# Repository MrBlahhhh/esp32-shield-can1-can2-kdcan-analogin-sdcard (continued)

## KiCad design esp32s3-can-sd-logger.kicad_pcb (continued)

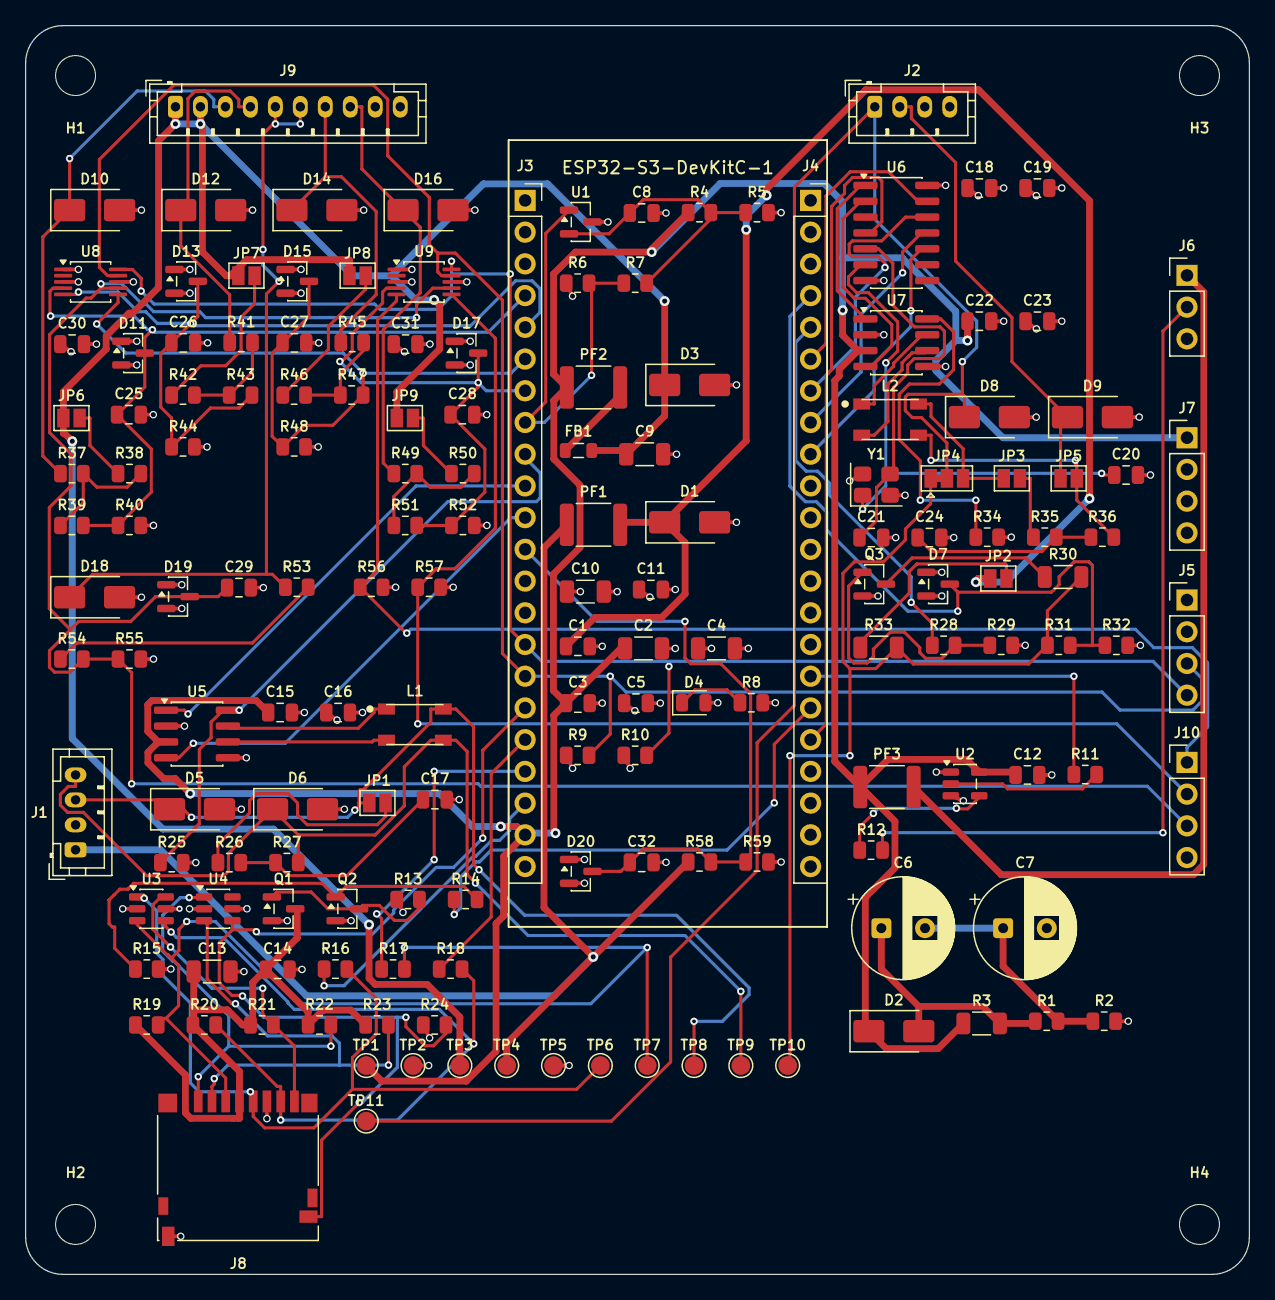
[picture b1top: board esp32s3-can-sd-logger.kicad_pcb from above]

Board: 4 copper layers, 98.0 x 100.0 mm, 164 parts (0 on the bottom side), 88 nets.

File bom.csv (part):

Qty (1 board),Qty (10 boards),References,Value,Voltage,Tolerance,Footprint,Manufacturer part number,LCSC,Notes
1,10,C1,100nF,100V,,Capacitor_SMD:C_0805_2012Metric,,C28233,
2,20,C17 C24,4.7nF,50V,,Capacitor_SMD:C_0805_2012Metric,,C1744,Split-termination common-mode stabiliser
1,10,C19,1uF,16V,,Capacitor_SMD:C_0805_2012Metric,,C28323,MCP2518FD bulk
2,20,C2 C4,22uF,16V,,Capacitor_SMD:C_1206_3216Metric,,C12891,Bulk at the 5 V socket pin
2,20,C20 C21,15pF,50V,,Capacitor_SMD:C_0805_2012Metric,,C1794,"Crystal load cap, sized for Y1's 12 pF CL: C1=C2=2*(CL - Cstray) = 2*(12 - 5) = 14 pF, and 15 pF is the nearest E-series value. Re-check this if the crystal is substituted -- CL varies part to part, and an oscillator that starts on the bench but not at -20 C is the classic way to get it wrong"
5,50,C25 C26 C27 C28 C29,470nF,50V,,Capacitor_SMD:C_0805_2012Metric,,C13967,"Ch1 anti-alias. 470nF, not the 100nF this inherited: source impedance here is (1k+10k)||2.21k = 1.84k, so 100nF puts the corner at 865 Hz -- above the 430 Hz Nyquist of the ADS1115 at 860 SPS, and well above anything the ESP32's own SAR ADC can sample cleanly. That was survivable while 0-5 V was the default range (261 Hz) and became the only behaviour when the range jumpers went. 470nF gives 184 Hz, which still passes anything a wideband does and stops engine noise folding into the log"
13,130,C11 C12 C14 C15 C16 C18 C22 C23 C3 C30 C31 C32 C5,100nF,16V,,Capacitor_SMD:C_0805_2012Metric,,C49678,
2,20,C6 C7,0.33F,2.7V,,Capacitor_THT:CP_Radial_D8.0mm_P3.50mm,Eaton HB1030-2R5105-R,,"Hold-up cell 1 of 2 in series -> 0.165 F at 5.4 V, which is 825 ms with the strip shed. 1 F was the first pick and bought 2500 ms that nothing needs: the parent board shipped 127 ms and that was judged adequate, a healthy card flushes in 18 ms, and the worst stall gen/simulate_firmware.py models is 500 ms. This is still six times the parent's margin and it is the most expensive line on the board -- see docs/COST.md. ESR must be under about 1 ohm; cylindrical cells are around 200 mohm, coin-type EDLCs are 30-200 OHM and will not work here"
1,10,C8,1nF,50V,,Capacitor_SMD:C_0805_2012Metric,,C46653,Keeps switching noise off the reference
3,30,C10 C13 C9,10uF,16V,,Capacitor_SMD:C_1206_3216Metric,,C13585,
5,50,D1 D5 D6 D8 D9,SMAJ26CA,,,Diode_SMD:D_SMA,Diodes Inc SMAJ26CA-13-F,C134976,"Clamps the OBD 12 V node. 400 W is enough here, not the parent's 1500 W SMC: nothing downstream draws more than 25 mA, so there is no load-dump energy to carry into a converter -- only a clamp to hold"
5,50,D10 D12 D14 D16 D18,SMAJ40CA,,,Diode_SMD:D_SMA,Littelfuse SMAJ40CA,C223989,"Ch1 harness transient clamp (bidirectional, 400W)"
1,10,D2,SS14,,,Diode_SMD:D_SMA,SS14,C2480,"Discharge path, bypassing the charge resistor. Anode on the bank, cathode on the rail: it conducts only once the rail has sagged a diode drop below the bank, which is exactly when the supply has gone away"
1,10,D3,SMAJ6.0A,,,Diode_SMD:D_SMA,Littelfuse SMAJ6.0A,C223993,"Clamps harness-injected transients on the sensor 5V. 6.0V standoff, not 5.0V: a 5.0V part on a 5.0V rail leaks up to 800uA continuously"
1,10,D4,green,,,LED_SMD:LED_0805_2012Metric,,C2297,"Shield 3V3 is up, which means the dev board is in its socket the right way round and its LDO is running"
7,70,D11 D13 D15 D17 D19 D20 D7,BAT54S,,,Package_TO_SOT_SMD:SOT-23,MDD BAT54S,C408389,"RX clamp. This one is not optional -- it conducts on every recessive bit above 11.5 V of battery, which is most of them"
1,10,FB1,600R,,,Inductor_SMD:L_0805_2012Metric,Wurth 742792022,C2661452,
4,40,H1 H2 H3 H4,M3,,,MountingHole:MountingHole_3.2mm_M3,,,
1,10,J1,CAN1 + power harness,,,Connector_JST:JST_PH_B4B-PH-K_1x04_P2.00mm_Vertical,JST B4B-PH-K-S(LF)(SN),C131334,"OBD-II pins 16/4/6/14. Pin 1 is sense only -- the board is powered from the dev board's USB-C, not from here"
1,10,J10,Spare diff in,,,Connector_PinHeader_2.54mm:PinHeader_1x04_P2.54mm_Vertical,,,"The second ADC's unused pair, brought out raw -- 0-3.3V only, no divider and no clamp in front of them. For a bench sensor, not for the loom"
1,10,J2,Aux bus harness,,,Connector_JST:JST_PH_B4B-PH-K_1x04_P2.00mm_Vertical,JST B4B-PH-K-S(LF)(SN),C131334,"The second port. What these two pins carry is a solder-jumper choice: K-line on AUX_A (the default, which is what an R53 wants), or the second CAN pair. See AUXSEL and AUXCL on the CAN sheet"
1,10,J3,DevKit J1,,,Connector_PinSocket_2.54mm:PinSocket_1x22_P2.54mm_Vertical,ESP32-S3-DevKitC-1 J1,,"Mirrors DevKitC-1 J1. Pins 1-2 (3V3) and 21 (5V) are both INPUTS to the shield. Analog on 4-7 and 12, CAN on 9-11, SD bus on 15-20 -- grouped so each block routes away from the row rather than across it. Pin 3 is RST, pins 13/14 are IO3/IO46, all left open."
1,10,J4,DevKit J3,,,Connector_PinSocket_2.54mm:PinSocket_1x22_P2.54mm_Vertical,ESP32-S3-DevKitC-1 J3,,"Mirrors DevKitC-1 J3. K-line on 4/5, the second CAN's SPI on 6-9 with its interrupt on 18, WS2812 on 16. Pin 17 is SD_PWR_EN, the one net that crosses to the other side of the board, and it goes round the end of the row. Pin 10 (IO38) is left open because it drives the dev board's RGB LED on v1.1; check the revision, some put it on IO48, which is the WS2812 output here."
1,10,J5,I2C / Qwiic,,,Connector_PinHeader_2.54mm:PinHeader_1x04_P2.54mm_Vertical,,,External I2C sensors. Kept because the dev board has no Qwiic connector of its own
1,10,J6,WS2812,,,Connector_PinHeader_2.54mm:PinHeader_1x03_P2.54mm_Vertical,,,Shift-light header: +5V / 5V-logic DIN / GND
1,10,J7,Rail break-out,,,Connector_PinHeader_2.54mm:PinHeader_1x04_P2.54mm_Vertical,,,
1,10,J8,microSD push-pull,,,Connector_Card:microSD_HC_Hirose_DM3D-SF,Hirose DM3D-SF,C719027,Push-pull socket; DET is the card-present switch
1,10,J9,Sensor harness,,,Connector_JST:JST_PH_B10B-PH-K_1x10_P2.00mm_Vertical,JST B10B-PH-K-S(LF)(SN),C158038,"Two 5V excitation pins, two Kelvin sense-ground pins, two current-carrying grounds, four signals. SENS_RTN must land on the SENSOR's ground stud, not on the same stud as pins 9/10"
1,10,JP1,TERM,,,Jumper:SolderJumper-2_P1.3mm_Open_Pad1.0x1.5mm,,,"Ships OPEN: unterminated. Bridge the pads only when this board is an END node on its own bus. A vehicle's bus -- OBD-II diagnostics included -- is already terminated at both ends, and a third 120 ohm across the pair takes it to about 40 ohm and can stop it working. Defaulting terminated made that an easy mistake to make"
1,10,JP2,KPU,,,Jumper:SolderJumper-2_P1.3mm_Open_Pad1.0x1.5mm,,,Ships OPEN. Bridge only if a module will not answer without a tester pull-up on the K-line
1,10,JP3,TERM2,,,Jumper:SolderJumper-2_P1.3mm_Open_Pad1.0x1.5mm,,,"Ships OPEN, for the same reason TERM does: a vehicle bus is already terminated at both ends"
1,10,JP4,AUXSEL,,,Jumper:SolderJumper-3_P1.3mm_Bridged12_Pad1.0x1.5mm,,,"Ships BRIDGED 1-2 = K-line on harness pin 5, which is what an R53 wants. For the second CAN instead: cut 1-2, bridge 2-3, and close AUXCL below. Both, or neither, is a bus that does not work"
1,10,JP5,AUXCL,,,Jumper:SolderJumper-2_P1.3mm_Open_Pad1.0x1.5mm,,,"The second half of AUXSEL. Open in K-line mode, which also leaves the second transceiver looking at an open circuit -- harmless, but firmware must not enable CAN2 there or it will bus-off waiting for an ACK that cannot come"
1,10,JP6,PULLUP1,,,Jumper:SolderJumper-2_P1.3mm_Open_Pad1.0x1.5mm,,,"Close for 2-wire NTC / open-collector sensors. Nothing to do with the input range -- it is about what kind of sensor is on the other end, not how many volts it swings"
1,10,JP7,PULLUP2,,,Jumper:SolderJumper-2_P1.3mm_Open_Pad1.0x1.5mm,,,"Close for 2-wire NTC / open-collector sensors. Nothing to do with the input range -- it is about what kind of sensor is on the other end, not how many volts it swings"
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
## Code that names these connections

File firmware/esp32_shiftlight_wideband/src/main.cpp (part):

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#define LED_TYPE    WS2812B
#define COLOR_ORDER GRB

#define CAN_TX_PIN  GPIO_NUM_17
#define CAN_RX_PIN  GPIO_NUM_18
#define CAN_S_PIN   16            // low = normal, high = listen-only

#define PWR_FAIL_PIN 15           // rising = the 5 V rail is below 4.20 V

// K-line, not yet driven. Listed so the pin map in this file stays the whole
// pin map -- a GPIO that is documented nowhere is a GPIO someone reuses.
#define K_TX_PIN      2           // low-side FET gate; UART TX must be inverted
#define K_RX_PIN      1           // divided 22k/10k and clamped

// Second CAN bus: an MCP2518FD on SPI, because the ESP32-S3 has exactly one
// TWAI peripheral and two buses have to be watched at once. Not driven by
// this sketch yet; listed so the pin map in this file stays the whole pin
// map. SDI/SDO on the controller are named from ITS point of view, so they
// cross over: the controller's SDI is this end's MOSI.
#define CAN2_SCK_PIN  39
#define CAN2_MOSI_PIN 40          // -> MCP2518FD SDI
#define CAN2_MISO_PIN 41          // <- MCP2518FD SDO
#define CAN2_CS_PIN   42
#define CAN2_INT_PIN  21
// These two live on the far socket row from the card itself. They are the
// only SD signals that do, and deliberately: they are DC, so crossing the
// board costs nothing, while the six bus lines stay beside the slot.
#define SD_PWR_EN_PIN 47
#define SD_CD_PIN     11
// 1-BIT SDMMC. D1/D2/D3 are not wired to the MCU at all: those three pins
// went to the second CAN controller's SPI bus, which needed five and had
// two spare. The card still pulls all three up -- a card samples DAT3 at
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// there. 1-bit carries about 1.5 MB/s against this logger's <130 kB/s, and
// bus width does not touch the card's internal write stall, which is the
// thing the whole hold-up budget is sized around.
#define SD_CLK_PIN 14
#define SD_CMD_PIN 13
#define SD_D0_PIN  12

#define RPM_STALE_MS 2000         // blank the strip if CAN goes quiet

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// worst case and the ADS1115's own 0.30% is the larger term. A per-channel
// calibration would still be better, but nothing here assumes you took one.
static const float DIVIDER_GAIN = 5.9774f;
static const int   ESP_ADC_PIN  = 4;       // AIN1 = GPIO4 = ADC1_CH3
static const int   VBAT_ADC_PIN = 8;       // VBAT_SNS = GPIO8, from OBD-II pin 16
// 108.2k / 8.2k, not the 11.0 this file inherited. The schematic moved to
// 13.2:1 so a 36 V input would not saturate the ADC and the constant never
// followed, so every battery reading was 20 % low. The fwsim board model
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  // CAN_S low = normal mode. R40 already pulls it there so the transceiver is
  // sane while the MCU is in reset; drive it anyway so the state is the
  // firmware's decision and not a resistor's.
  pinMode(CAN_S_PIN, OUTPUT);
  digitalWrite(CAN_S_PIN, LOW);

  twai_general_config_t g =
      TWAI_GENERAL_CONFIG_DEFAULT(CAN_TX_PIN, CAN_RX_PIN, TWAI_MODE_NORMAL);
  g.rx_queue_len = 32;   // FastLED.show() blocks ~0.5 ms; don't drop frames in it
  twai_timing_config_t t = TWAI_TIMING_CONFIG_500KBITS();
  twai_filter_config_t f = TWAI_FILTER_CONFIG_ACCEPT_ALL();
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
// --- microSD -----------------------------------------------------------------
void sdInit() {
  pinMode(SD_CD_PIN, INPUT);
  pinMode(SD_PWR_EN_PIN, OUTPUT);
  digitalWrite(SD_PWR_EN_PIN, HIGH);       // the card supply is switched
  delay(10);                               // let the rail come up before clocking

  SD_MMC.setPins(SD_CLK_PIN, SD_CMD_PIN, SD_D0_PIN);
  if (!SD_MMC.begin("/sdcard", true)) {    // 1-bit; see the pin block above
    Serial.println("SD: mount failed");
    return;
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
/**
 * The firmware half of README section 2. The hardware guarantees roughly
 * 108 ms between PWR_FAIL and the converters dropping out; this is what spends
 * it. Order matters: the sensor rail is already off (the ISR did it), the strip
 * goes dark so it is not drawing from the bank, then the file is closed, and
 * only then is the card supply removed — with SD_MMC.end() first, because
 * dropping SD_PWR_EN while the bus pins are still driven back-feeds the card
 * through its ESD structures (README section 5).
 */
void shutdown() {
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    SD_MMC.end();
    sdUp = false;
  }
  digitalWrite(SD_PWR_EN_PIN, LOW);

  Serial.printf("PWR_FAIL at %lu ms: %lu lines flushed and closed\n", millis(), logLines);
}
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  // Armed before anything slow runs. An ignition cut during BLE bring-up is
  // still an ignition cut, and the card is not open yet but the interrupt
  // still has to be the thing that shuts the rail down.
  pinMode(PWR_FAIL_PIN, INPUT);
  attachInterrupt(digitalPinToInterrupt(PWR_FAIL_PIN), onPowerFail, RISING);

  // BLE goes first, on purpose. The BT controller wants a sizeable block of
  // internal RAM (it cannot use PSRAM) and it is the one subsystem here that
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
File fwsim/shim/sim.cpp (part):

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    fault(SEV_ERROR, "PIN_PSRAM", "GPIO%d driven, but it is octal PSRAM on this module", gpio);
  if (p && p->role == ROLE_SD_PWR_EN && level == 0 && s.sd_begun)
    fault(SEV_WARN, "SD_BACKFEED",
          "SD_PWR_EN (GPIO%d) dropped while the card is still mounted. Call SD_MMC.end() first, "
          "or the MCU keeps driving the bus into an unpowered card through its ESD structures "
          "(README section 5)",
          gpio);
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  s.can_pins_ok = true;
  if (want_tx >= 0 && tx != want_tx) {
    const PinDef* p = find_pin(tx);
    fault(SEV_ERROR, "CAN_TX_PIN",
          "TWAI TX assigned to GPIO%d (%s), but this board wires the transceiver TXD to GPIO%d -- "
          "no frames will ever arrive, and GPIO%d is now driven by the CAN controller",
          tx, p ? role_name(p->role) : "not connected", want_tx, tx);
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  }
  if (want_rx >= 0 && rx != want_rx) {
    const PinDef* p = find_pin(rx);
    fault(SEV_ERROR, "CAN_RX_PIN",
          "TWAI RX assigned to GPIO%d (%s), but this board wires the transceiver RXD to GPIO%d",
          rx, p ? role_name(p->role) : "not connected", want_rx, rx);
    s.can_pins_ok = false;
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  int cs = gpio_with_role(ROLE_CAN_S);
  if (cs >= 0 && !pin_driven(cs))
    fault(SEV_NOTE, "CAN_S_DEFAULT",
          "CAN_S (GPIO%d) left undriven; R54 pulls it low so the transceiver comes up in normal "
          "mode. Drive it high for listen-only if this node must never ACK",
          cs);
}
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  s.i2c_pins_ok = true;
  if (want_sda >= 0 && sda != want_sda) {
    const PinDef* p = find_pin(sda);
    fault(SEV_ERROR, "I2C_SDA_PIN",
          "I2C SDA brought up on GPIO%d, but on this board GPIO%d is %s (%s) and the bus is on "
          "GPIO%d. Driving it toggles that function",
          sda, sda, p ? p->net : "nothing", p ? role_name(p->role) : "not connected", want_sda);
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  }
  if (want_scl >= 0 && scl != want_scl) {
    const PinDef* p = find_pin(scl);
    fault(SEV_ERROR, "I2C_SCL_PIN",
          "I2C SCL brought up on GPIO%d, but on this board GPIO%d is %s (%s) and the bus is on "
          "GPIO%d",
          scl, scl, p ? p->net : "nothing", p ? role_name(p->role) : "not connected", want_scl);
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  int pwr = gpio_with_role(ROLE_SD_PWR_EN);
  if (pwr >= 0 && !(s.level.count(pwr) && s.level[pwr] == 1)) {
    fault(SEV_ERROR, "SD_UNPOWERED",
          "SD_MMC.begin() with SD_PWR_EN (GPIO%d) low -- the card supply is switched through "
          "Q2/Q3 and off at reset, so there is no card on the bus to answer",
          pwr);
    return false;
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  s.stop_reason = why ? why : "";
  if (s.pwr_fail_at_ms >= 0.0 && !s.pwr_fail_observed)
    fault(SEV_ERROR, "PWR_FAIL_IGNORED",
          "PWR_FAIL (GPIO%d) asserted at %.1f ms and firmware never read it or attached an "
          "interrupt to it. The hardware buys a %.0f ms window to shed the sensor rail and close "
          "the file; nothing in this firmware spends it",
          gpio_with_role(ROLE_PWR_FAIL), s.pwr_fail_at_ms, board().ridethru_shed_ms);
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
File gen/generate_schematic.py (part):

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    So a label at 180 needs `right` to run its text away from the wire it
    came in on. Eight were emitted with a hardcoded `left` from the block
    tables and ran backwards over the very part they named: "AGND_SENSE"
    printed through the ADS1115's pin 1, "I2C_SDA" and "I2C_SCL" through the
    socket pins beside them.
    """
    return "right" if int(angle) % 360 in (180, 270) else "left"
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         "8": "PWR_FAIL",
         # --- CAN block ---
         "9": "CAN_S", "10": "CAN_TX", "11": "CAN_RX",
         "12": "VBAT_SNS",           # IO8, the fifth ADC1 pin
         # 13 (IO3) and 14 (IO46) are strapping pins and stay unconnected.
         # --- I2C, then the microSD bus, at the bottom of the row ---
         "15": "I2C_SCL", "16": "I2C_SDA",
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     },
     mpn="ESP32-S3-DevKitC-1 J3",
     note="Mirrors DevKitC-1 J3. K-line on 4/5, the second CAN's SPI on "
          "6-9 with its interrupt on 18, WS2812 on 16. Pin 17 is SD_PWR_EN, "
          "the one net that crosses to the other side of the board, and it "
          "goes round the end of the row. Pin 10 (IO38) is left open because it drives the "
          "dev board's RGB LED on v1.1; check the revision, some put it on "
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C(cn, "4.7nF 50V", "CAN2_SPLIT", "GND", note="Split-termination common-mode stabiliser")

# ---- which one reaches the harness --------------------------------------
# AUX_A and AUX_B are harness pins 5 and 6. They carry either the K-line or
# the second CAN pair, never both -- K-line idles at battery voltage and a
# CAN transceiver biases its bus to 2.5 V, so the two cannot share a wire.
#
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            # Owning the net means the block's wires reach every pin on it --
            # not merely that every part is a member. The microSD connector
            # belongs to the SD block, but its VDD pin is fanned out to a
            # label like its eight neighbours, so SD_VDD is still a name the
            # sheet shares and has to be written as a global.
            elsewhere = {(p["ref"], num) for s2 in SHEETS for p in s2["parts"]
                         for num, v in p["pins"].items()
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
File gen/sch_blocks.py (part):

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        # value      nets                           dx      dy   rot
        ("10k",    {"K_TX", "K_TX_G"},           -19.05,   0.00,  90),
        ("100k",   {"K_TX_G", "GND"},             -8.89,   8.89,   0),
        # 180: pin 1 is K_TX_D and has to face the drain below it,
        # pin 2 is K_LINE and has to reach the bus above.
        ("20",     {"K_TX_D", "K_LINE"},           2.54, -16.51, 180),
        ("22k",    {"K_LINE", "K_RX"},            12.70, -13.97,   0),
        ("10k",    {"K_RX", "GND"},               12.70,  -2.54,   0),
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        [(57.15, 45.72), (57.15, 41.91)],        # name spur
    ],
    "junctions": [(57.15, 45.72)],
    "labels": {"PWR_LED_K": (57.15, 41.91, 90)},
}


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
